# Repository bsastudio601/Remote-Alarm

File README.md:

# Remote Alarm 
remote alarm is an alarm clock that is also a multipurpose controller! it can be used to play games, control rc vehicles, can act as a console!

# Screenshots!
## CAD

## Schematic

## PCB

## Case top and bottom

## Firmware
I used the example code for the display and copied section of the clock code from another repo : https://github.com/word9317/hopOffBro/tree/main/Firmware 
and cleaned it up to use for my clock.

## BOM

| Component | Quantity |
|-----------|----------|
| Seeed Studio esp 32c3 | 1x |
| MX-Style Switch | 6x |
| 1N4148 Diode | 6x |
| Blank DSA keycaps | 6x | 
| 2.25Inch TFT Display | 1x | 
| 2.54mm 8 Pin Male Header | 1x | 
| 3.3V piezo Buzzer | 1x |
| M3x8mm Screws | 4x |
| M3x16mm Screws | 4x |
| M3x5mx4mm heatset inserts  |8x | 
| Custom PCB | 1x |
| 3D printed case | 1x |

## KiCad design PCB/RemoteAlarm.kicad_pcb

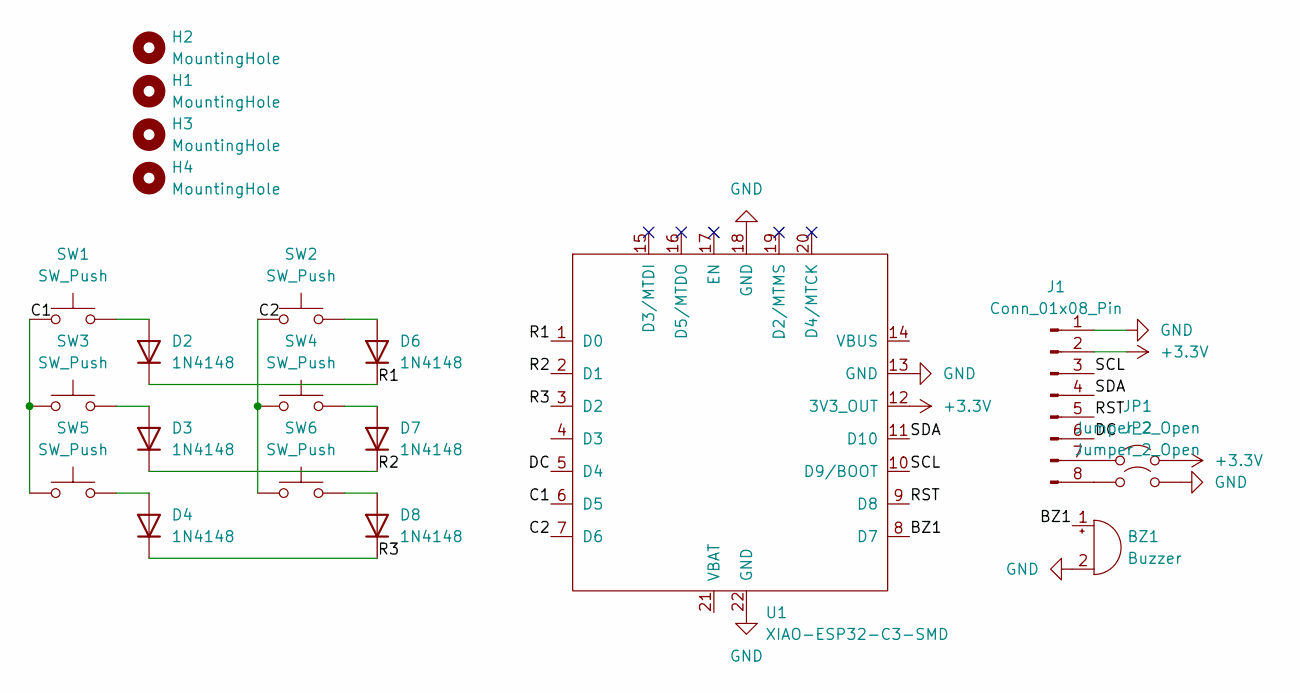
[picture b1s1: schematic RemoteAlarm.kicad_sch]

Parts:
BZ1: Buzzer; Buzzer_12x9.5RM7.6
D2, D3, D4, D6, D7, D8: 1N4148; D_DO-35_SOD27_P7.62mm_Horizontal
H1, H2, H3, H4: MountingHole; MountingHole_3.2mm_M3
J1: Conn_01x08_Pin; PinSocket_1x08_P2.54mm_Vertical
JP1, JP2: Jumper_2_Open; SolderJumper-2_P1.3mm_Open_Pad1.0x1.5mm
SW1, SW2, SW3, SW4, SW5, SW6: SW_Push; SW_Cherry_MX_1.00u_PCB
U1: XIAO-ESP32-C3-SMD; XIAO-ESP32-C3-DIP-SMD

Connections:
+3.3V: J1.2, JP1.2 (B), U1.12 (3V3_OUT)
/BZ1: BZ1.1 (+), U1.8 (D7)
/C1: SW1.1, SW3.1, SW5.1, U1.6 (D5)
/C2: SW2.1, SW4.1, SW6.1, U1.7 (D6)
/DC: J1.6, U1.5 (D4)
/R1: D2.1 (K), D6.1 (K), U1.1 (D0)
/R2: D3.1 (K), D7.1 (K), U1.2 (D1)
/R3: D4.1 (K), D8.1 (K), U1.3 (D2)
/RST: J1.5, U1.9 (D8)
/SCL: J1.3, U1.10 (D9/BOOT)
/SDA: J1.4, U1.11 (D10)
GND: BZ1.2 (-), J1.1, JP2.2 (B), U1.13 (GND), U1.18 (GND), U1.22 (GND)
unnamed: D2.2 (A), SW1.2
unnamed: D3.2 (A), SW3.2
unnamed: D4.2 (A), SW5.2
unnamed: D6.2 (A), SW2.2
unnamed: D7.2 (A), SW4.2
unnamed: D8.2 (A), SW6.2
unnamed: J1.7, JP1.1 (A)
unnamed: J1.8, JP2.1 (A)

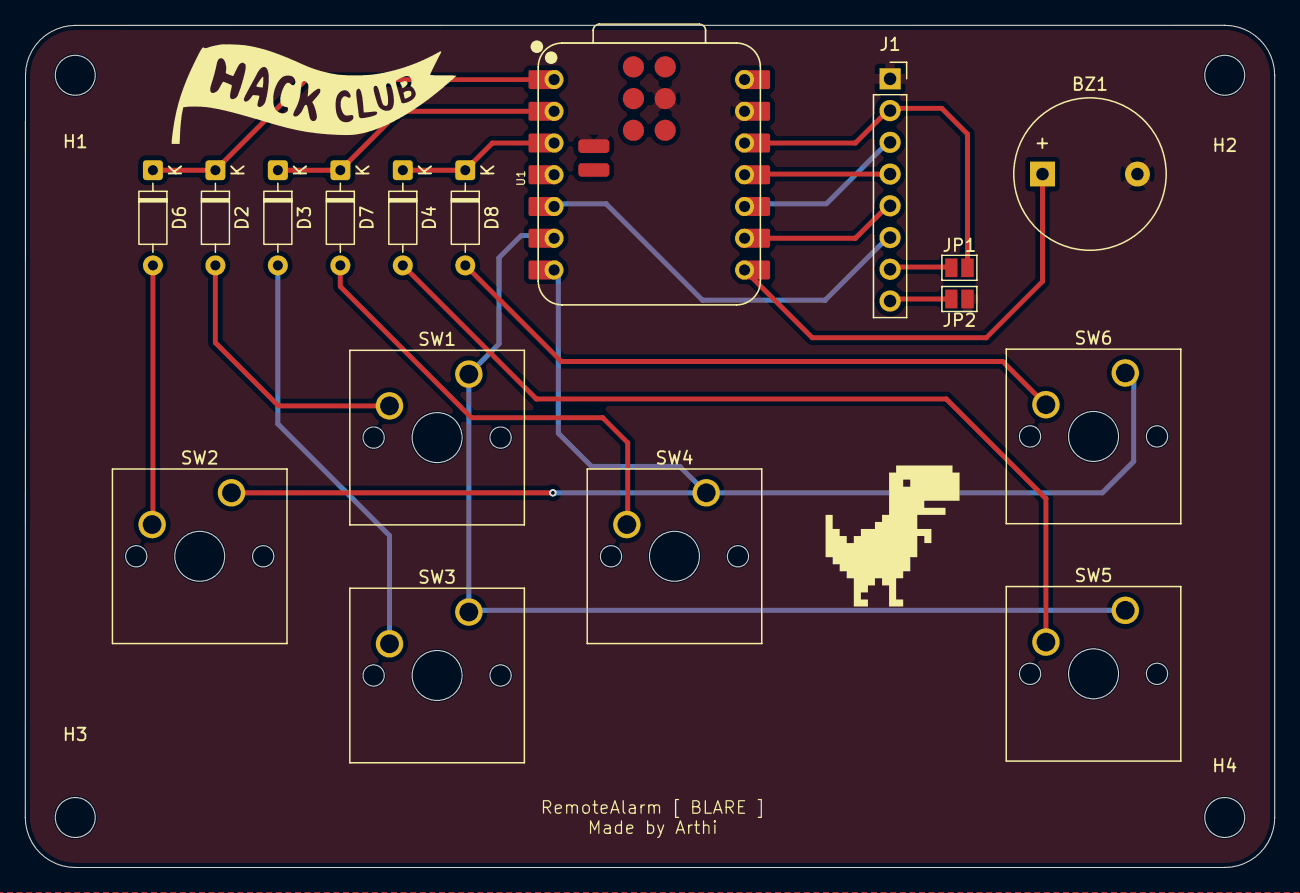
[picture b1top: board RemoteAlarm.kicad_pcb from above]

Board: 4 copper layers, 100.0 x 67.4 mm, 21 parts (0 on the bottom side), 20 nets.
